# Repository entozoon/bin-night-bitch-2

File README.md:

# bin-night-bitch-2
Indicates when and which bins to put out! Configurable this time, with RTC

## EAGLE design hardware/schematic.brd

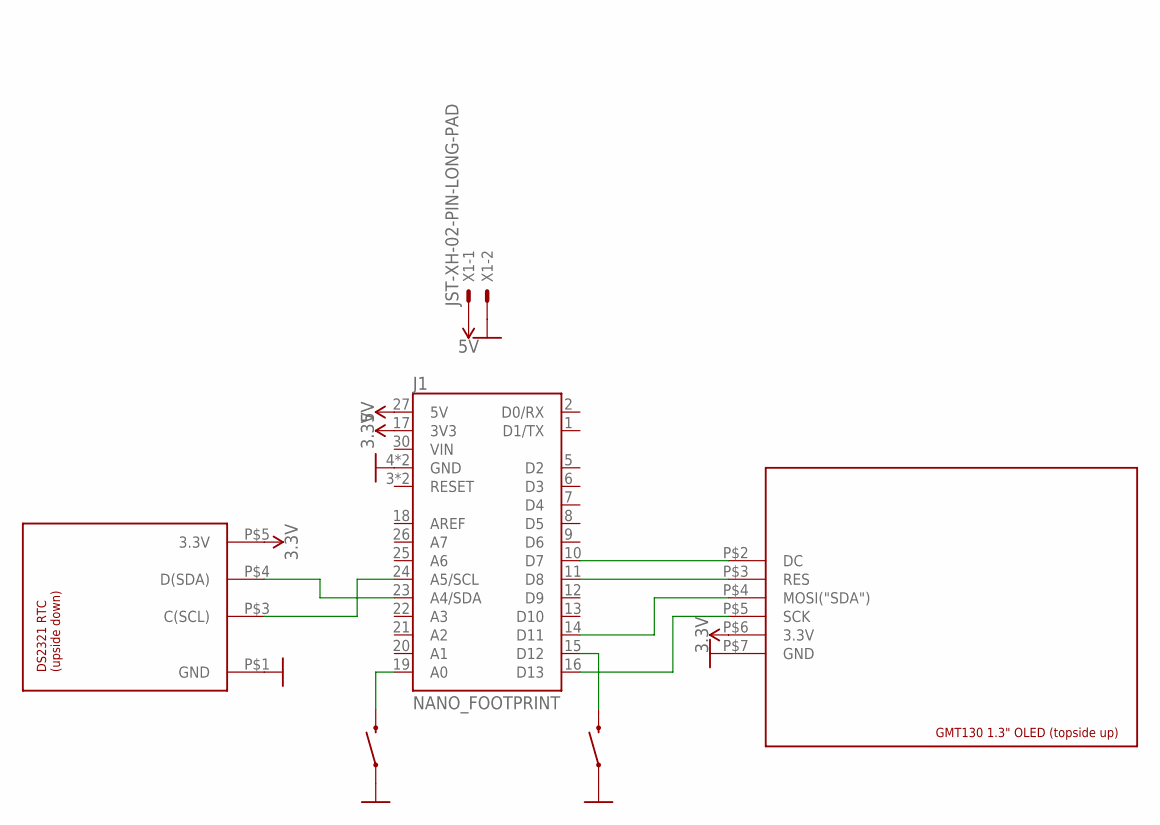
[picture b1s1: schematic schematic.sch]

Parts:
J1: NANO_FOOTPRINT; NANO
S1, S2: MOMENTARY-SWITCH-SPST-SMD-4.6X2.8MM; TACTILE_SWITCH_SMD_4.6X2.8MM
U$1: GMT130-1.3-OLED
U$2: DS2321-RTC
X1: JST-XH-02-PIN-LONG-PAD; JST-XH-02-PACKAGE-LONG-PAD

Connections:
3.3V: J1.17 (3V3), U$1.P$6 (3.3V), U$2.P$5 (3.3V)
5V: J1.27 (5V), X1.1
GND: J1.4 (GND), J1.29 (GND), S1.1, S1.2 (1), S2.1, S2.2 (1), U$1.P$7 (GND), U$2.P$1 (GND), X1.2
unnamed: J1.23 (A4/SDA), U$2.P$4 (D(SDA))
unnamed: J1.24 (A5/SCL), U$2.P$3 (C(SCL))
unnamed: J1.11 (D8), U$1.P$3 (RES)
unnamed: J1.10 (D7), U$1.P$2 (DC)
unnamed: J1.14 (D11), U$1.P$4 (MOSI("SDA"))
unnamed: J1.16 (D13), U$1.P$5 (SCK)
unnamed: J1.19 (A0), S2.3 (2), S2.4 (2)
unnamed: J1.15 (D12), S1.3 (2), S1.4 (2)

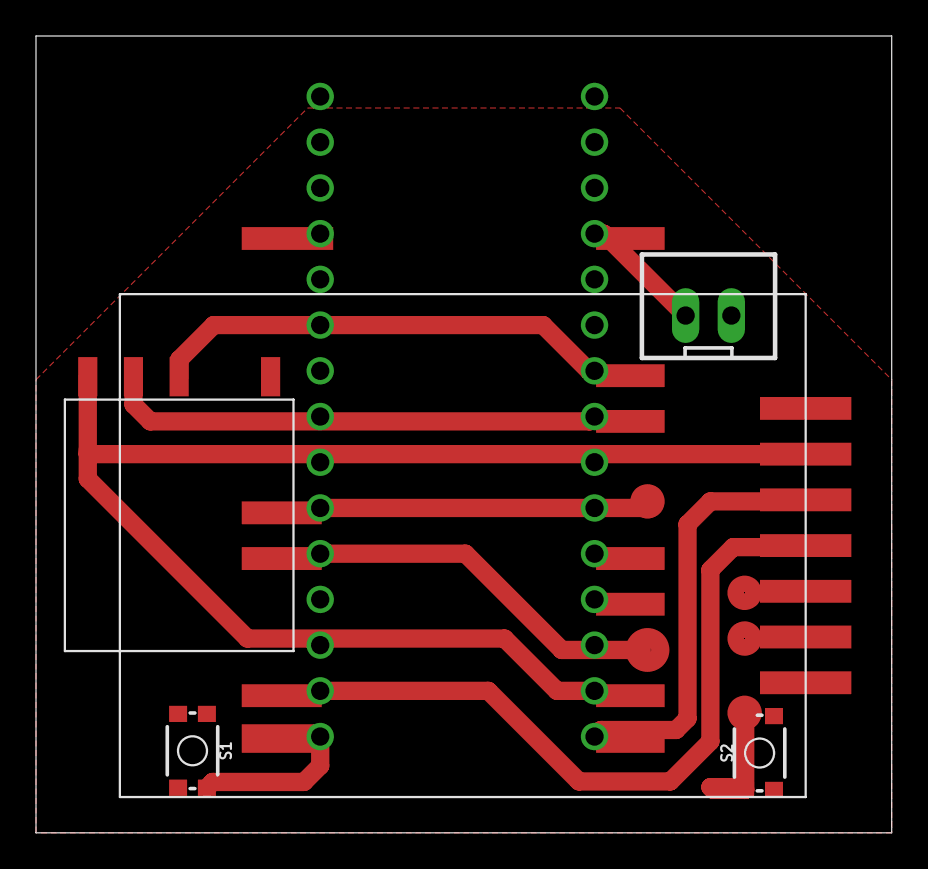
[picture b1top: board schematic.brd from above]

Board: 2 copper layers, 47.5 x 44.3 mm, 6 parts (0 on the bottom side), 11 nets.

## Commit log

2020-11-12 Platformio blink for Nano
2020-11-12 Working LCD test, took ages to get pins right but hey ho
2020-11-13 Hardware built
2020-11-14 Coding up real nice already
2020-11-14 Next steps note
2020-11-16 Actual functional menu system, blowing my own mind over here
2020-11-17 Date time all saving and nice
2020-11-19 I think I've boshed it
2020-11-19 Ternary errors, it's always ternary errors

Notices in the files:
parts and their libraries:
SparkFun-Boards: Licensing: Creative Commons ShareAlike 4.0 International - https://creativecommons.org/licenses/by-sa/4.0
